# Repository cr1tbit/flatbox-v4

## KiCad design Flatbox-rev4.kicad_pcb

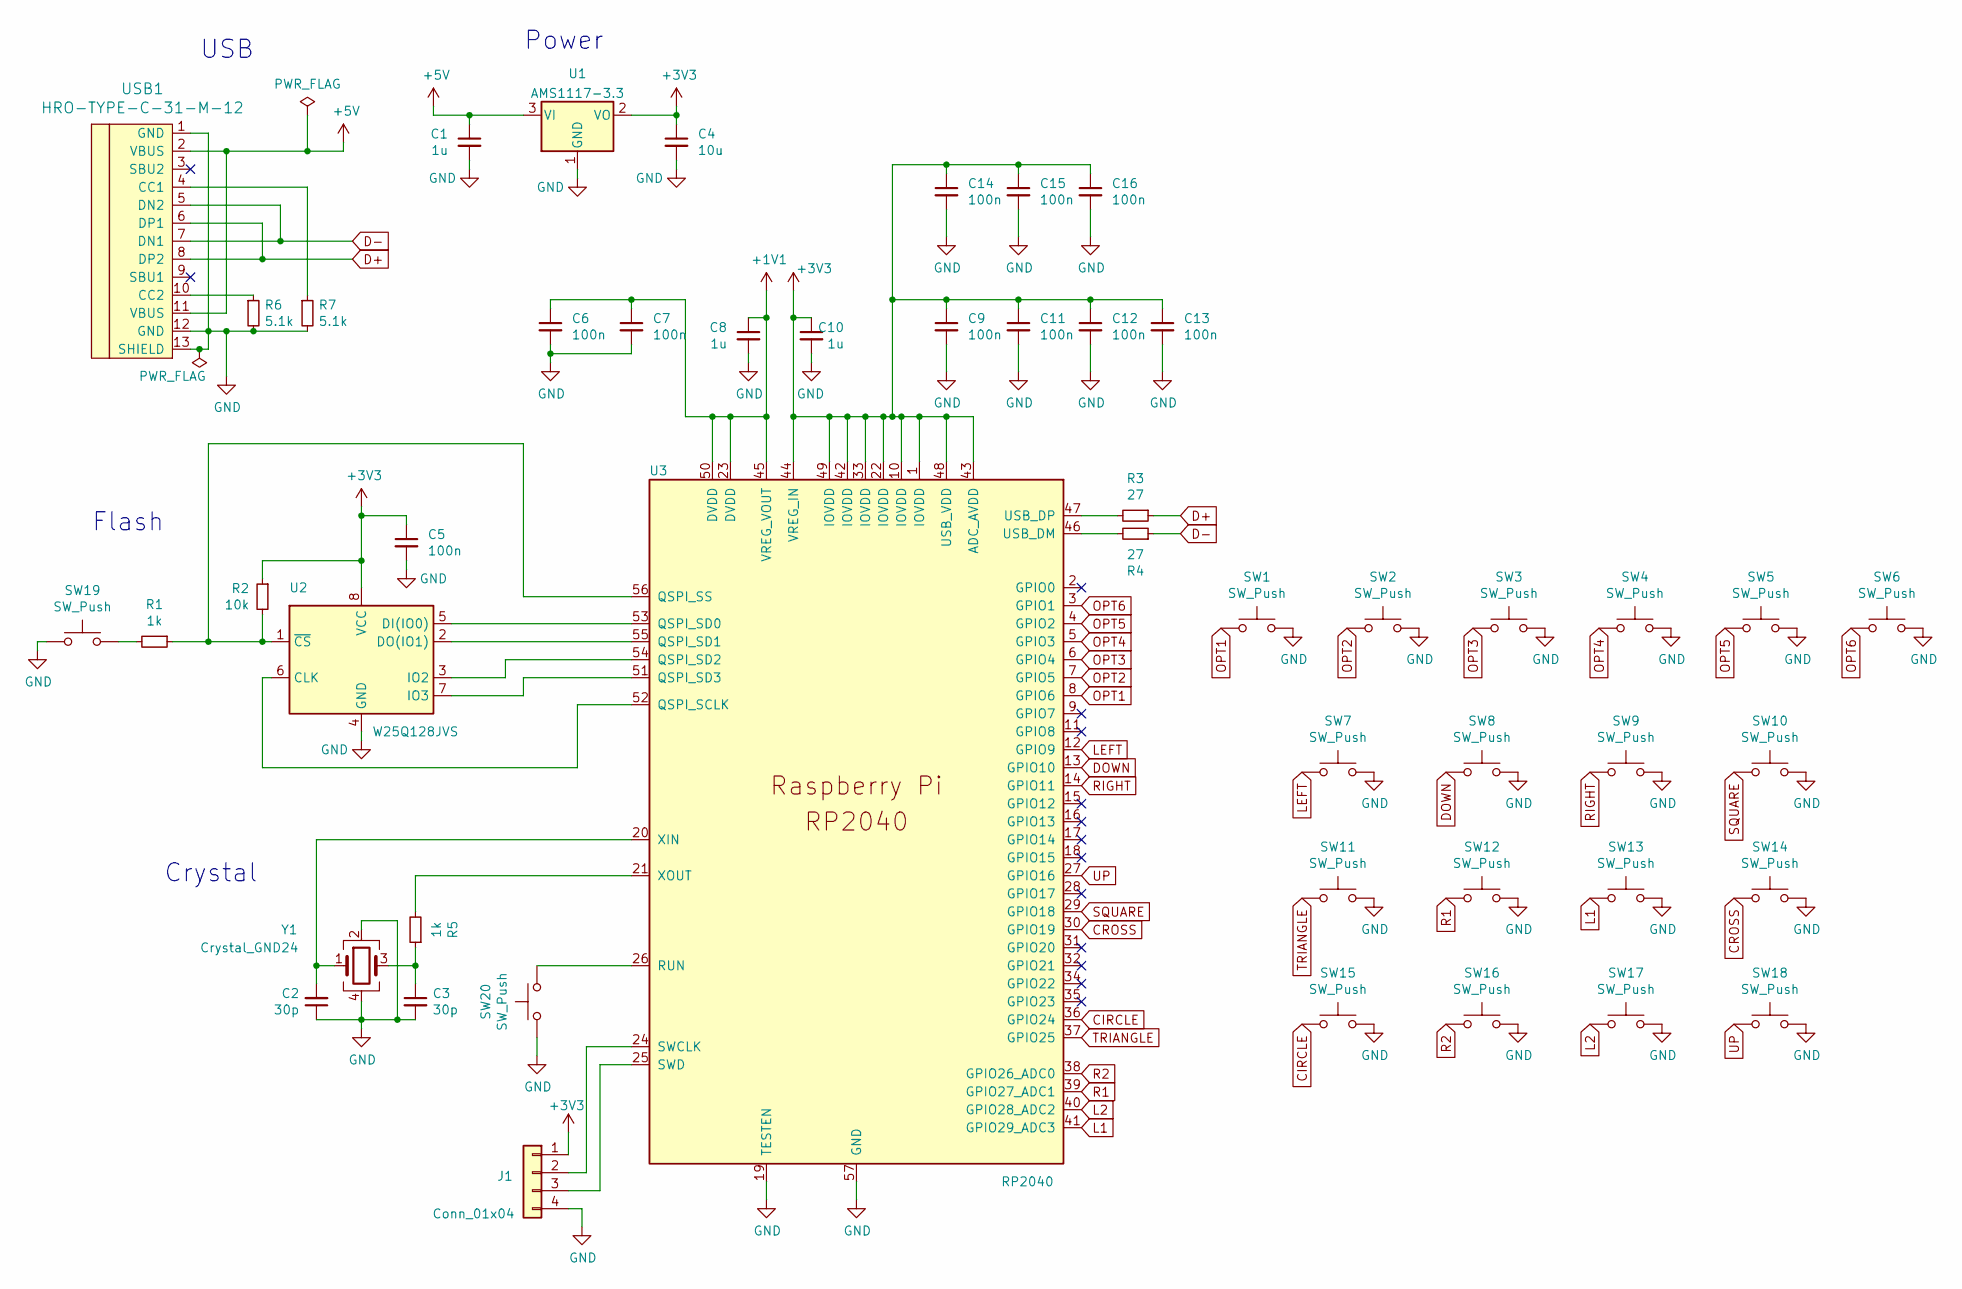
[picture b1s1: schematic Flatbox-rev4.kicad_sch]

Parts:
C1, C8, C10: 1u; C_0402_1005Metric; LCSC C52923
C2, C3: 30p; C_0402_1005Metric; LCSC C1570
C4: 10u; C_0603_1608Metric; LCSC C52923
C5, C6, C7, C9, C11, C12, C13, C14, C15, C16: 100n; C_0402_1005Metric; LCSC C1525
J1: Conn_01x04; PinHeader_1x04_P2.54mm_Vertical
R1, R5: 1k; R_0402_1005Metric; LCSC C11702
R2: 10k; R_0402_1005Metric; LCSC C25744
R3, R4: 27; R_0402_1005Metric; LCSC C138021
R6, R7: 5.1k; R_0402_1005Metric; LCSC C25905
SW1, SW2, SW3, SW4, SW5, SW6: SW_Push; SW_PUSH_6mm_H5mm
SW7, SW8, SW9, SW10, SW11, SW12, SW13, SW14, SW15, SW16, SW17, SW18: SW_Push; Kailh_socket_PG1350_optional
SW19, SW20: SW_Push; SW_SPST_Omron_B3FS-100xP; LCSC C271750
U1: AMS1117-3.3; SOT-223-3_TabPin2
U2: W25Q128JVS; SOIC-8_5.23x5.23mm_P1.27mm; LCSC C97521
U3: RP2040; RP2040-QFN-56; LCSC C2040
USB1: HRO-TYPE-C-31-M-12; HRO-TYPE-C-31-M-12-Assembly; LCSC C165948
Y1: Crystal_GND24; Crystal_SMD_3225-4Pin_3.2x2.5mm; LCSC C9002

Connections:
+1V1: C6.1, C7.1, C8.1, U3.23 (DVDD), U3.45 (VREG_VOUT), U3.50 (DVDD)
+3V3: C4.1, C5.1, C9.1, C10.1, C11.1, C12.1, C13.1, C14.1, C15.1, C16.1, J1.1, R2.1, U1.2 (VO), U2.8 (VCC), U3.1 (IOVDD), U3.10 (IOVDD), U3.22 (IOVDD), U3.33 (IOVDD), U3.42 (IOVDD), U3.43 (ADC_AVDD), U3.44 (VREG_IN), U3.48 (USB_VDD), U3.49 (IOVDD)
+5V: C1.1, U1.3 (VI), USB1.2 (VBUS), USB1.11 (VBUS)
CIRCLE: SW15.1, U3.36 (GPIO24)
CROSS: SW14.1, U3.30 (GPIO19)
D+: R3.1, USB1.6 (DP1), USB1.8 (DP2)
D-: R4.1, USB1.5 (DN2), USB1.7 (DN1)
DOWN: SW8.1, U3.13 (GPIO10)
GND: C1.2, C2.1, C3.2, C4.2, C5.2, C6.2, C7.2, C8.2, C9.2, C10.2, C11.2, C12.2, C13.2, C14.2, C15.2, C16.2, J1.4, R6.2, R7.2, SW1.2, SW2.2, SW3.2, SW4.2, SW5.2, SW6.2, SW7.2, SW8.2, SW9.2, SW10.2, SW11.2, SW12.2, SW13.2, SW14.2, SW15.2, SW16.2, SW17.2, SW18.2, SW19.1, SW20.1, U1.1 (GND), U2.4 (GND), U3.19 (TESTEN), U3.57 (GND), USB1.1 (GND), USB1.12 (GND), USB1.13 (SHIELD), Y1.2, Y1.4
L1: SW13.1, U3.41 (GPIO29_ADC3)
L2: SW17.1, U3.40 (GPIO28_ADC2)
LEFT: SW7.1, U3.12 (GPIO9)
unnamed: C3.1, R5.1, Y1.3
unnamed: R1.2, SW19.2
unnamed: R3.2, U3.47 (USB_DP)
unnamed: R4.2, U3.46 (USB_DM)
unnamed: R6.1, USB1.10 (CC2)
unnamed: R7.1, USB1.4 (CC1)
unnamed: U2.6 (CLK), U3.52 (QSPI_SCLK)
unnamed: C2.2, U3.20 (XIN), Y1.1
unnamed: R5.2, U3.21 (XOUT)
unnamed: J1.2, U3.24 (SWCLK)
unnamed: J1.3, U3.25 (SWD)
unnamed: SW20.2, U3.26 (RUN)
unnamed: U2.7 (IO3), U3.51 (QSPI_SD3)
unnamed: U2.5 (DI(IO0)), U3.53 (QSPI_SD0)
unnamed: U2.3 (IO2), U3.54 (QSPI_SD2)
unnamed: U2.2 (DO(IO1)), U3.55 (QSPI_SD1)
unnamed: R1.1, R2.2, U2.1 (~CS), U3.56 (QSPI_SS)
OPT1: SW1.1, U3.8 (GPIO6)
OPT2: SW2.1, U3.7 (GPIO5)
OPT3: SW3.1, U3.6 (GPIO4)
OPT4: SW4.1, U3.5 (GPIO3)
OPT5: SW5.1, U3.4 (GPIO2)
OPT6: SW6.1, U3.3 (GPIO1)
R1: SW12.1, U3.39 (GPIO27_ADC1)
R2: SW16.1, U3.38 (GPIO26_ADC0)
RIGHT: SW9.1, U3.14 (GPIO11)
SQUARE: SW10.1, U3.29 (GPIO18)
TRIANGLE: SW11.1, U3.37 (GPIO25)
UP: SW18.1, U3.27 (GPIO16)

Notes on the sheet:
Flash
Crystal
USB
Power

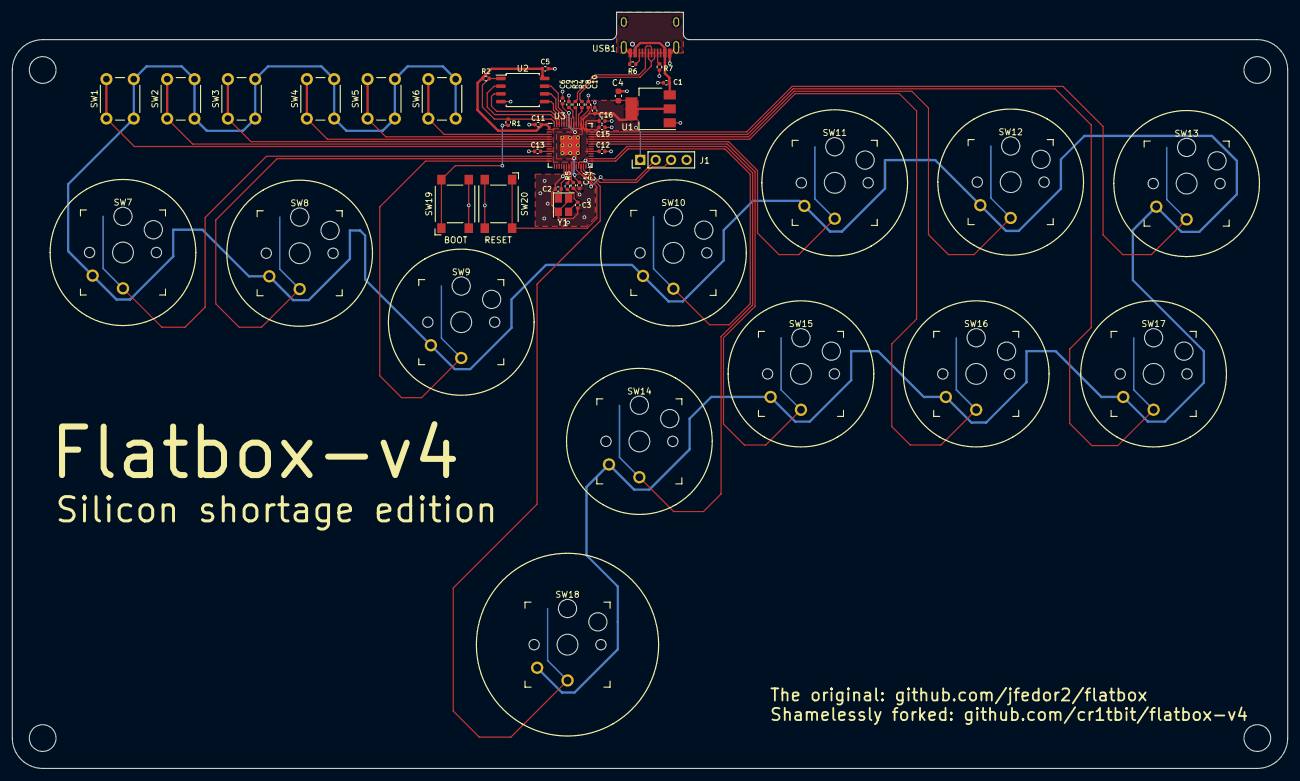
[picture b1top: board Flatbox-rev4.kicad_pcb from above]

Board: 2 copper layers, 210.0 x 124.5 mm, 49 parts (0 on the bottom side), 41 nets.

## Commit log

2022-05-09 repo init
2022-06-02 adding poc scad 3d models
